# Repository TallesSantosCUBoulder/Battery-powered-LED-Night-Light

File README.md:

# LED Night Light — Educational Project

The **LED Night Light** is a compact, energy-efficient device that automatically turns on in darkness and turns off under bright ambient light using a **photoresistor (LDR)** in a voltage-divider circuit. This project introduces students to fundamental electronics concepts such as current-limiting resistors, voltage dividers, photoresistor behavior, and sensor-based control. It is designed for hands-on learning within the CU Boulder / CMU Partnership Program.

---

## Breadboard Prototype

The circuit is first built on a **breadboard** for testing, experimentation, and debugging. Using basic components—resistors, an LED, a photoresistor, a battery, and jumper wires—students can verify their wiring and observe how the LED responds as light levels change.

<p align="center"><em>Figure 1: Breadboard setup of the LED Night Light.</em></p>

---

## PCB Implementation

Once the prototype is validated, the design can be transferred to a **PCB (Printed Circuit Board)** for a more permanent and reliable build. The PCB is designed for **tool-free assembly**: students simply insert and bend component leads into the pre-defined holes (no soldering required). This reinforces skills such as reading PCB silkscreens, identifying components, and performing clean mechanical assembly.

<p align="center"><em>Figure 2: Assembled PCB version of the Battery-Powered LED Night Light.</em></p>

---

## Educational Goals

This project reinforces foundational concepts, including:

- Operation of LEDs and basic semiconductor behavior
- Light-dependent resistors (LDRs) as analog sensors
- Voltage dividers and threshold-based activation
- Power and energy considerations in low-power circuits
- PCB layout interpretation and hands-on component placement

The end result is a functional night light that demonstrates the interaction between sensing and simple electronic control.

---

# Quick Start

## Components

To build the Battery-Powered LED Night Light, you will need:

- **1 × LED**
- **1 × Photoresistor (LDR)**
- **1 × 4.7 kΩ resistor** (for the voltage divider)
- **1 × 220 Ω resistor** (LED current-limiting)
- **1 × 1/2 AA Size LS Battery (ER14250)**
- **1 × LED Night Light PCB**

<p align="center"><em>Figure 3: Components for the Battery-Powered LED Night Light.</em></p>

### Resistor Identification

<p align="center"><em>Figure 4: Resistor color-coding reference.</em></p>

---

## Assembly

Insert each component into its corresponding location on the PCB as indicated below. Ensure proper orientation for polarity-sensitive parts.

<p align="center"><em>Figure 5: PCB component placement guide.</em></p>

### LED Polarity

LEDs must be oriented correctly to function. The **long leg (anode)** is positive, and the **flat side** marks the negative lead (cathode).

<p align="center"><em>Figure 6: LED polarity reference.</em></p>

---

# License

This project is released under the **MIT License**.

---

# Disclaimer & Safety Notice

This activity is intended for **educational use only**, supporting hands-on learning in basic electronics. Follow all assembly instructions carefully and handle components and tools responsibly. The pliers used for bending component leads may have sharp edges—use them with caution.

This device is **not a toy** and must be used only in safe, supervised environments. Keep all components away from heat sources, moisture, and small children. The author and the CU Boulder / CMU Partnership Program are **not responsible for injury, damage, or malfunction** resulting from misuse or improper handling of the materials.

While creativity and experimentation are encouraged, **safety is the top priority**. Always verify circuit connections before inserting the battery, and avoid touching conductive parts while the device is powered. Any modifications to the original design should be performed under supervision or after consulting an instructor.

For additional protection, it is recommended that users wear **safety glasses** during assembly to prevent injury caused by component leads or tool slips. Please note that safety glasses are **not provided** as part of this activity.

By participating, users acknowledge that they are responsible for their own safety and agree to use the materials only for instructional, non-commercial purposes.

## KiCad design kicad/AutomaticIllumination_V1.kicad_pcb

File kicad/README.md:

# Battery-Powered LED Night Light

As part of my classes in the **CU Boulder / CMU Partnership Program**, students were challenged to design and build a **Battery-Powered LED Night Light** circuit.  
This activity combined theoretical knowledge with practical circuit design skills, providing students with hands-on experience in electronics assembly and testing.

The project also served a special purpose beyond the classroom.  
Students designed the LED night light as a **souvenir for future students**, especially high school visitors interested in engineering.  
Each group first built and tested the circuit on a breadboard, then transferred it to a printed circuit board (PCB) for a permanent and professional version—promoting technical learning, creativity, and teamwork within the CU Boulder / CMU Partnership Program.

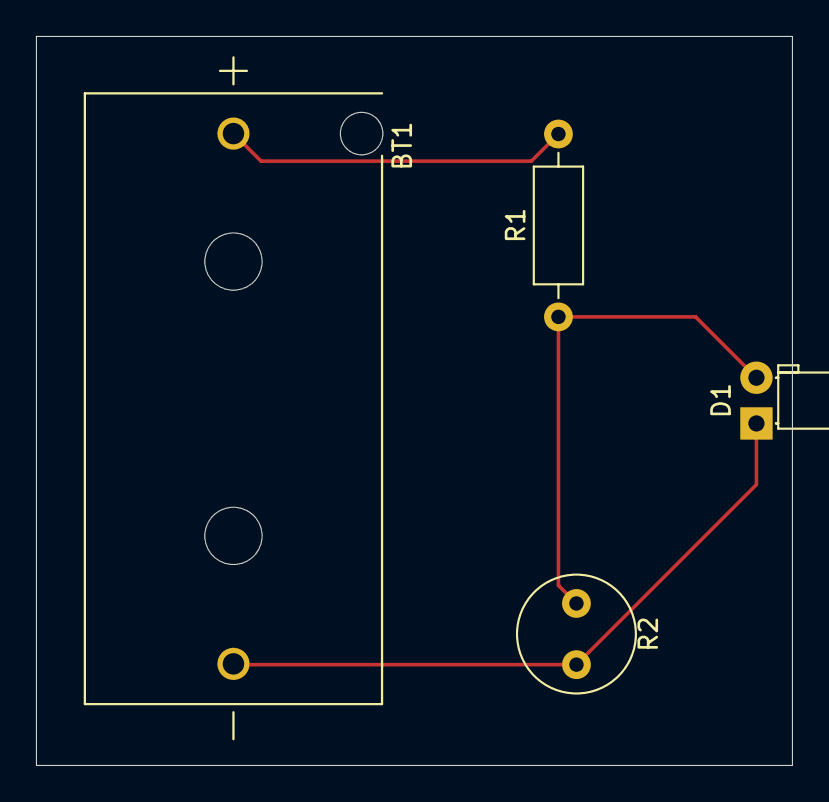
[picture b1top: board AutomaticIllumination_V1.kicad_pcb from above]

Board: 2 copper layers, 42.0 x 40.5 mm, 4 parts (0 on the bottom side), 3 nets.

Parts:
BT1: 815-0931; BAT_815-0931
D1: LED; LED_D3.0mm_Horizontal_O1.27mm_Z6.0mm
R1: 4.6k; R_Axial_DIN0207_L6.3mm_D2.5mm_P10.16mm_Horizontal
R2: A1050; R_LDR_D6.4mm_P3.4mm_Vertical

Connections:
unnamed: BT1.+, R1.2
unnamed: D1.2 (A), R1.1, R2.1
unnamed: BT1.-, D1.1 (K), R2.2

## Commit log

2025-11-06 Testing commit using Linux terminal.
2025-11-06 Update the manual
2025-11-06 Remove low resolution manual
2025-11-19 Add a short tutorial in the README showing how to assemble the PCB.
